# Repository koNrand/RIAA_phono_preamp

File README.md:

# RIAA compatible phono preamp

based on information from an [article](https://hifi.de/feature/technik-erklaert-phono-vorverstaerker-56652) from hifi.de I designed an phono preamp for my turn table.
The project contains an simulation of the equalizing circuit with an amplifier. 
In the KiCad project is 34x72mm PCB with rounded edges so the circuit fits in standard IP54 75x35x40mm cable boxes.
The final stereo circuit comes with with an adjustable amplification from 0dB to 60dB for both channel, and USB-A jack as power input and RCA jack inputs.

The `reichelt_special_components_list.csv` contains the most special component and a link to a public list, so you can order than from reichelt.de or look them up and order them whereever you want.

fair use only, open hardware FTW <3

useful links:
- [KiCad](kicad.org/), a free and open source schematic and PCB layout design software, comes with endless awesome plugins. -> a selfmade basics [Tutorial](https://www.youtube.com/watch?v=UdfuM1iF3_Y&list=PLFoTc99xXplq-vwjNqq9S3VKb1se5qiRt) from my friend [Max](https://github.com/backtail)
- [LTSpice](https://www.analog.com/en/design-center/design-tools-and-calculators/ltspice-simulator.html), a free and powerfull SPICE simulation tool for simulating schematics with a graphical UI -> a selfmade basics [Tutorial]([https://www.youtube.com/watch?v=UdfuM1iF3_Y&list=PLFoTc99xXplq-vwjNqq9S3VKb1se5qiRt](https://www.youtube.com/watch?v=mdhnJGWT1hw&list=PLFoTc99xXplqWKGfDIrEuYwgaC7r6RATd)) from my friend [Max](https://github.com/backtail)
- a opamp [Tutorial](https://www.youtube.com/watch?v=Iz0e1WipaIw&list=PLFoTc99xXplpeMX_rCe2f8oruM441F54b) made by myself to be ready to understand, identify and use most important opamp circuits, comes with an practical example and how to use lab bench power supplies, script included in the video description

all tutorials are in german language

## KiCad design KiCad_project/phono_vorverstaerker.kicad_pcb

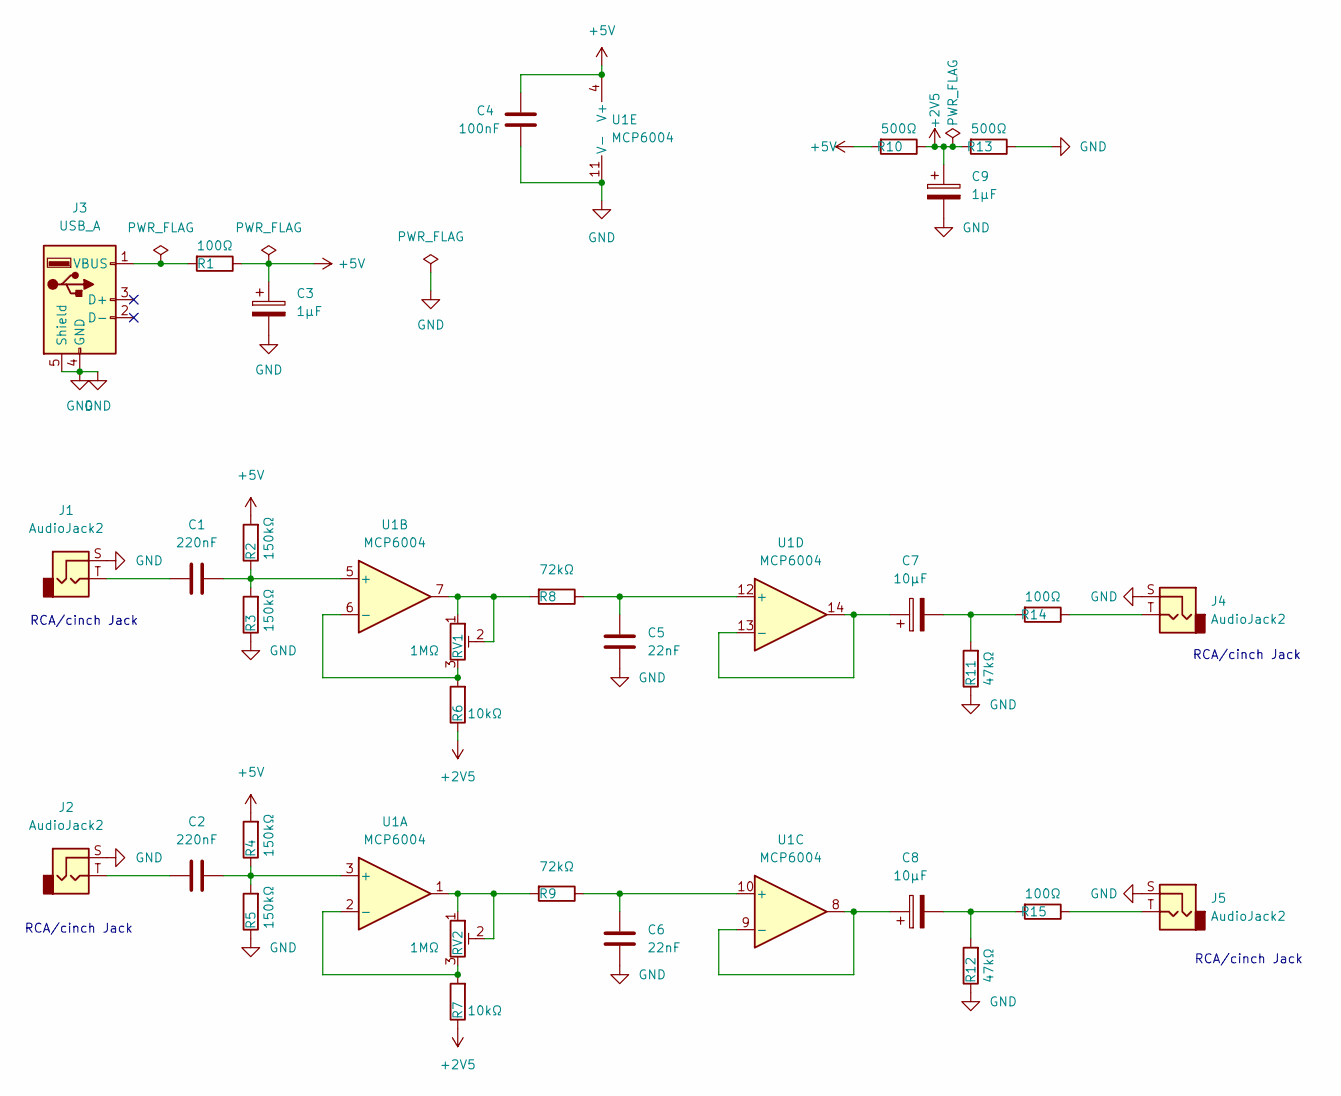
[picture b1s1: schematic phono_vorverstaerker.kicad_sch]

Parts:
C1, C2: 220nF; C_Disc_D3.4mm_W2.1mm_P2.50mm
C3, C9: 1µF; CP_Radial_D5.0mm_P2.50mm
C4: 100nF; C_Disc_D3.4mm_W2.1mm_P2.50mm
C5, C6: 22nF; C_Disc_D3.4mm_W2.1mm_P2.50mm
C7, C8: 10µF; CP_Radial_D5.0mm_P2.50mm
J1, J2, J4, J5: AudioJack2; cinch_einbaubuchse_CBP_G
J3: USB_A; USB_B_Lumberg_2411_02_Horizontal
R1, R14, R15: 100Ω; R_Axial_DIN0204_L3.6mm_D1.6mm_P7.62mm_Horizontal
R2, R3, R4, R5: 150kΩ; R_Axial_DIN0204_L3.6mm_D1.6mm_P7.62mm_Horizontal
R6, R7: 10kΩ; R_Axial_DIN0204_L3.6mm_D1.6mm_P7.62mm_Horizontal
R8, R9: 72kΩ; R_Axial_DIN0204_L3.6mm_D1.6mm_P7.62mm_Horizontal
R10, R13: 500Ω; R_Axial_DIN0204_L3.6mm_D1.6mm_P7.62mm_Horizontal
R11, R12: 47kΩ; R_Axial_DIN0204_L3.6mm_D1.6mm_P7.62mm_Horizontal
RV1, RV2: 1MΩ; Potentiometer_Bourns_3296W_Vertical
U1: MCP6004; DIP-14_W7.62mm

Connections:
+2V5: C9.1, R6.1, R7.1, R10.1, R13.2
+5V: C3.1, C4.2, R1.1, R2.2, R4.2, R10.2, U1.4 (V+)
GND: C3.2, C4.1, C5.1, C6.1, C9.2, J1.S, J2.S, J3.4 (GND), J3.5 (Shield), J4.S, J5.S, R3.1, R5.1, R11.1, R12.1, R13.1, U1.11 (V-)
unnamed: C1.1, J1.T
unnamed: C2.1, J2.T
unnamed: C7.2, R11.2, R14.2
unnamed: C8.2, R12.2, R15.2
unnamed: J3.1 (VBUS), R1.2
unnamed: J4.T, R14.1
unnamed: J5.T, R15.1
unnamed: R9.2, RV2.1, RV2.2, U1.1
unnamed: R7.2, RV2.3, U1.2 (-)
unnamed: C2.2, R4.1, R5.2, U1.3 (+)
unnamed: C1.2, R2.1, R3.2, U1.5 (+)
unnamed: R6.2, RV1.3, U1.6 (-)
unnamed: R8.2, RV1.1, RV1.2, U1.7
unnamed: C8.1, U1.8, U1.9 (-)
unnamed: C6.2, R9.1, U1.10 (+)
unnamed: C5.2, R8.1, U1.12 (+)
unnamed: C7.1, U1.13 (-), U1.14

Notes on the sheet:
RCA/cinch Jack

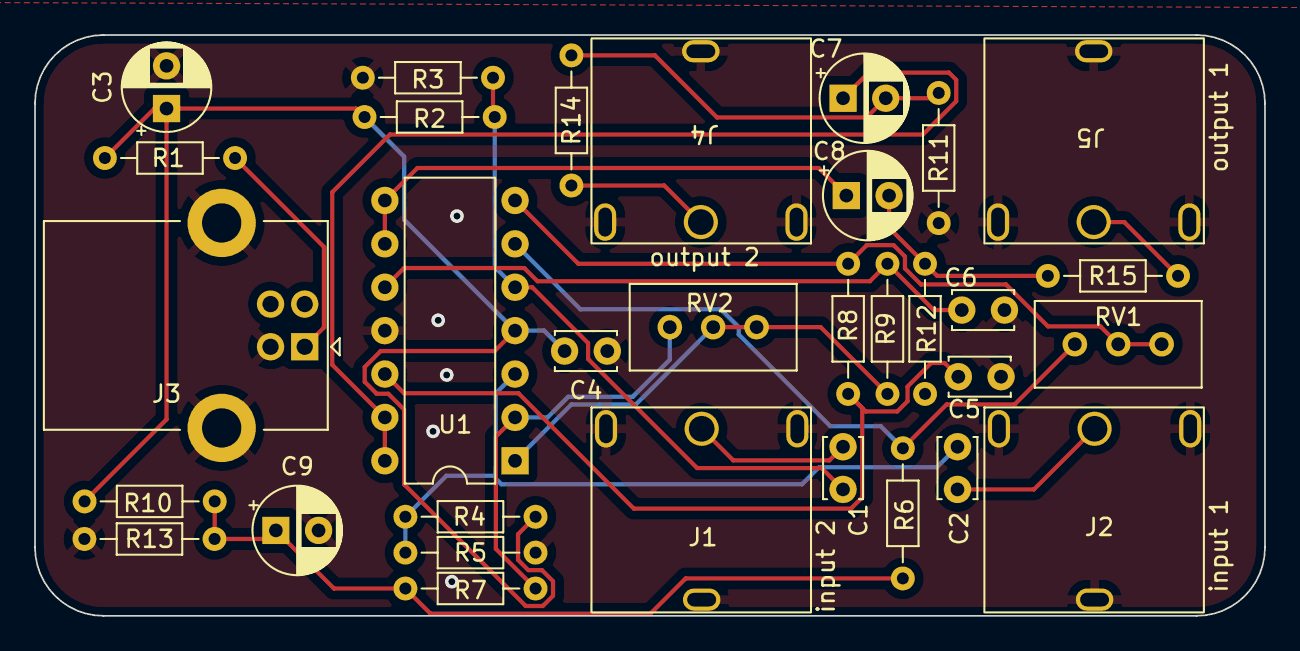
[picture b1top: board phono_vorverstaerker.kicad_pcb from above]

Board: 2 copper layers, 72.0 x 34.0 mm, 32 parts (0 on the bottom side), 20 nets.
